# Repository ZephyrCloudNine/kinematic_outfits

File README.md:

# kinematic_dress_hw_fw
Project files for custom "kinematic" dress that uses servos to move parts of it in a wavy motion.
Firmware uses an ESP32-C3 Devkit module.
Servos used - SG90 along with PCA9685 servo driver to extend servo drive functionality.
Mechanical design done on Fusion 360.

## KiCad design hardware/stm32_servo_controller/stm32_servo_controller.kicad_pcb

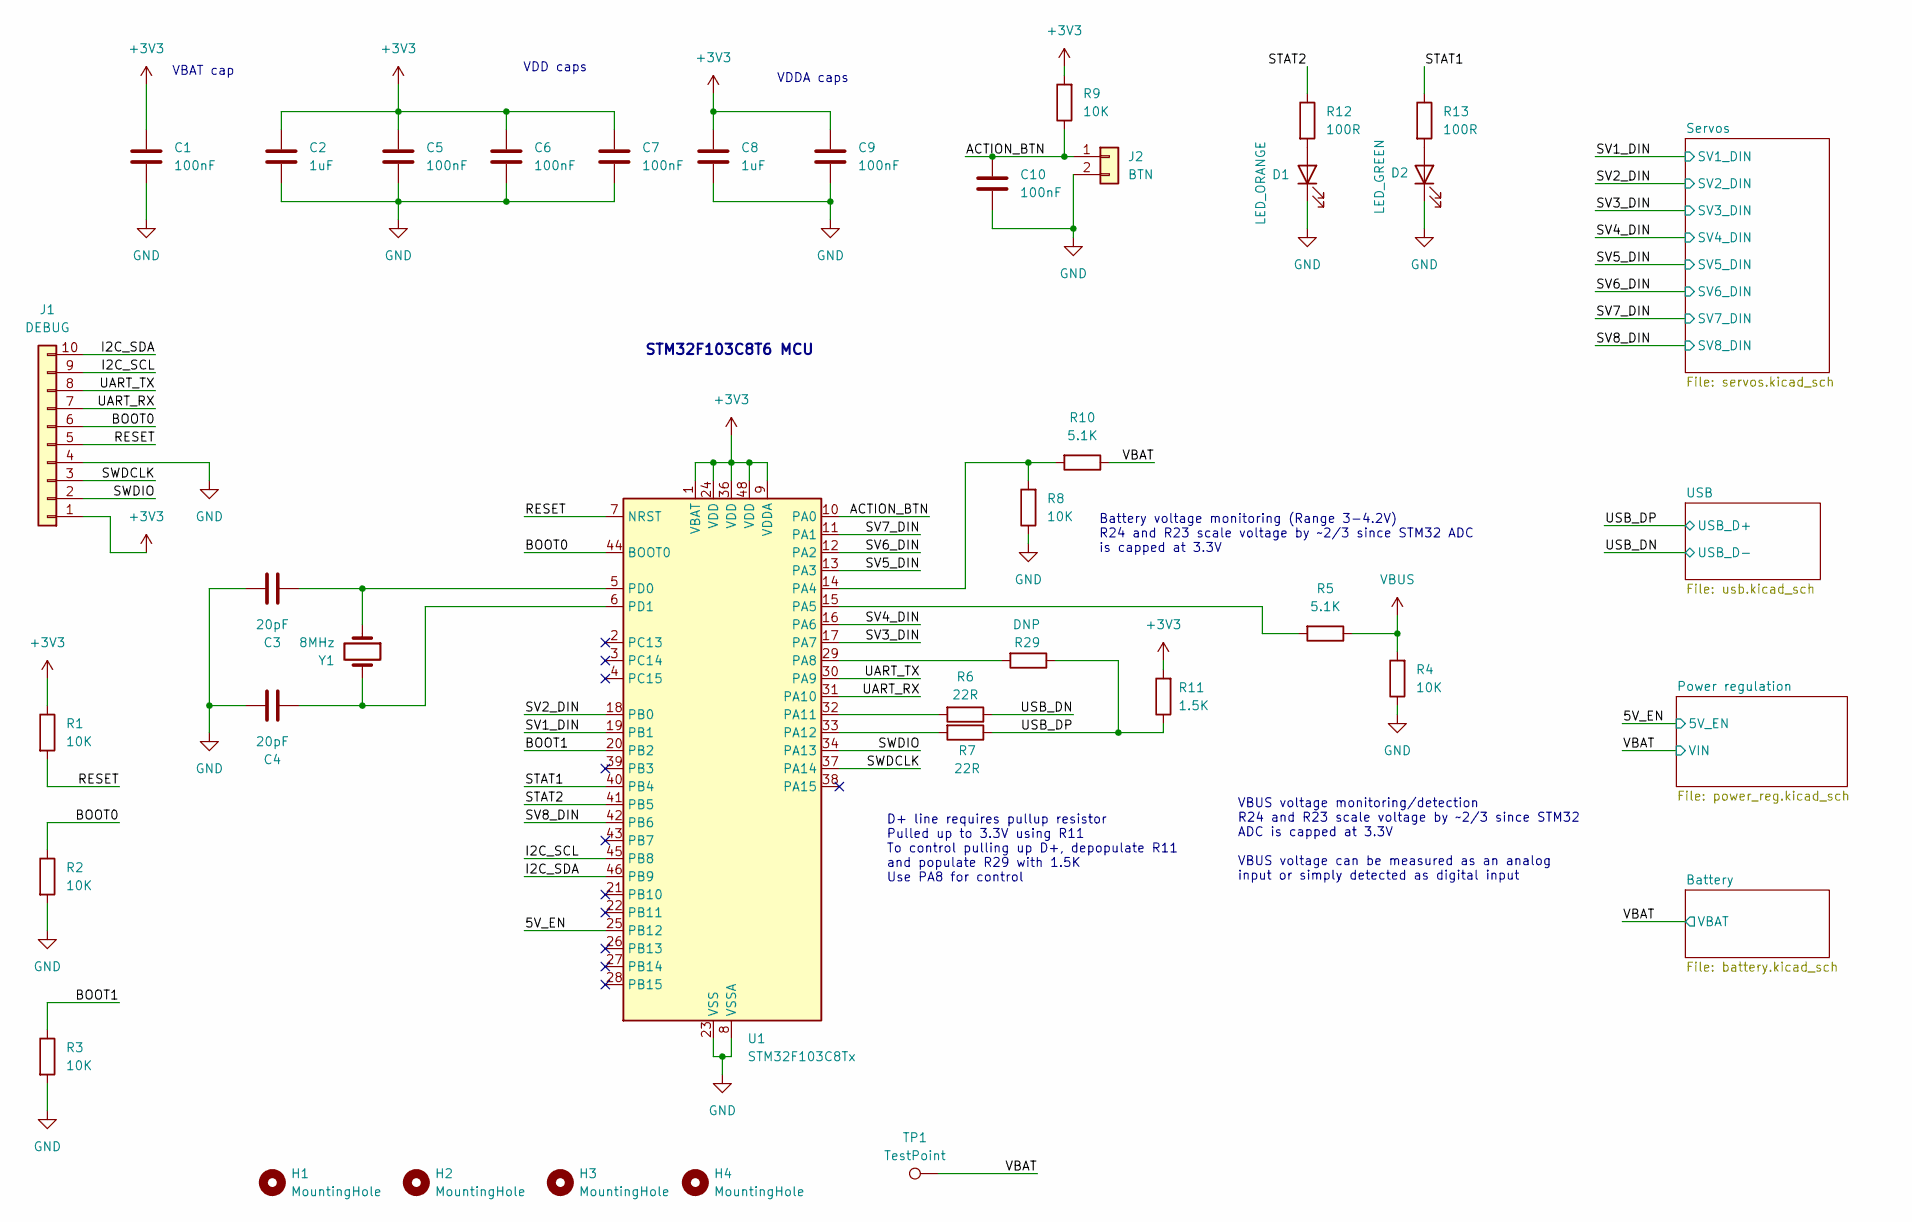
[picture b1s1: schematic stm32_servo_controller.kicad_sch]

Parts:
C1, C5, C6, C7, C9, C10: 100nF; C_0603_1608Metric
C2, C8: 1uF; C_0603_1608Metric
C3, C4: 20pF; C_0603_1608Metric
D1: LED_ORANGE; LED_0603_1608Metric
D2: LED_GREEN; LED_0603_1608Metric
H1, H2, H3, H4: MountingHole; MountingHole_3.2mm_M3
J1: DEBUG; PinHeader_1x10_P2.54mm_Vertical
J2: BTN; PinHeader_1x02_P2.54mm_Vertical
R1, R2, R3, R4, R8, R9: 10K; R_0603_1608Metric
R5, R10: 5.1K; R_0603_1608Metric
R6, R7: 22R; R_0603_1608Metric
R11: 1.5K; R_0603_1608Metric
R12, R13: 100R; R_0603_1608Metric
R29: DNP; R_0603_1608Metric
TP1: TestPoint; TestPoint_Pad_D1.0mm
U1: STM32F103C8Tx; LQFP-48_7x7mm_P0.5mm
Y1: 8MHz; Crystal_HC49-4H_Vertical

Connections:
+3V3: C1.1, C2.1, C5.1, C6.1, C7.1, C8.1, C9.1, J1.1, R1.1, R9.2, R11.2, U1.1 (VBAT), U1.9 (VDDA), U1.24 (VDD), U1.36 (VDD), U1.48 (VDD); also elsewhere on the board
/5V_EN: U1.25 (PB12); also elsewhere on the board
/ACTION_BTN: C10.1, J2.1, R9.1, U1.10 (PA0)
/BOOT0: J1.6, R2.1, U1.44 (BOOT0)
/BOOT1: R3.1, U1.20 (PB2)
/I2C_SCL: J1.9, U1.45 (PB8)
/I2C_SDA: J1.10, U1.46 (PB9)
/RESET: J1.5, R1.2, U1.7 (NRST)
/STAT1: R13.1, U1.40 (PB4)
/STAT2: R12.1, U1.41 (PB5)
/SV1_DIN: U1.19 (PB1); also elsewhere on the board
/SV2_DIN: U1.18 (PB0); also elsewhere on the board
/SV3_DIN: U1.17 (PA7); also elsewhere on the board
/SV4_DIN: U1.16 (PA6); also elsewhere on the board
/SV5_DIN: U1.13 (PA3); also elsewhere on the board
/SV6_DIN: U1.12 (PA2); also elsewhere on the board
/SV7_DIN: U1.11 (PA1); also elsewhere on the board
/SV8_DIN: U1.42 (PB6); also elsewhere on the board
/SWDCLK: J1.3, U1.37 (PA14)
/SWDIO: J1.2, U1.34 (PA13)
/UART_RX: J1.7, U1.31 (PA10)
/UART_TX: J1.8, U1.30 (PA9)
/USB_DN: R6.1; also elsewhere on the board
/USB_DP: R7.1, R11.1, R29.1; also elsewhere on the board
/VBAT: R10.1, TP1.1; also elsewhere on the board
GND: C1.2, C2.2, C3.2, C4.2, C5.2, C6.2, C7.2, C8.2, C9.2, C10.2, D1.1 (K), D2.1 (K), J1.4, J2.2, R2.2, R3.2, R4.1, R8.1, U1.8 (VSSA), U1.23 (VSS), U1.35 (VSS), U1.47 (VSS); also elsewhere on the board
unnamed: D1.2 (A), R12.2
unnamed: D2.2 (A), R13.2
unnamed: R8.2, R10.2, U1.14 (PA4)
unnamed: R5.2, U1.15 (PA5)
unnamed: R29.2, U1.29 (PA8)
unnamed: R6.2, U1.32 (PA11)
unnamed: R7.2, U1.33 (PA12)
unnamed: C3.1, U1.5 (PD0), Y1.1
unnamed: C4.1, U1.6 (PD1), Y1.2
VBUS: R4.2, R5.1; also elsewhere on the board

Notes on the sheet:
STM32F103C8T6 MCU
VDDA caps
VBAT cap
VDD caps
D+ line requires pullup resistor Pulled up to 3.3V using R11 To control pulling up D+, depopulate R11 and populate R29 with 1.5K Use PA8 for control
VBUS voltage monitoring/detection R24 and R23 scale voltage by ~2/3 since STM32 ADC is capped at 3.3V VBUS voltage can be measured as an analog input or simply detected as digital input
Battery voltage monitoring (Range 3-4.2V) R24 and R23 scale voltage by ~2/3 since STM32 ADC is capped at 3.3V

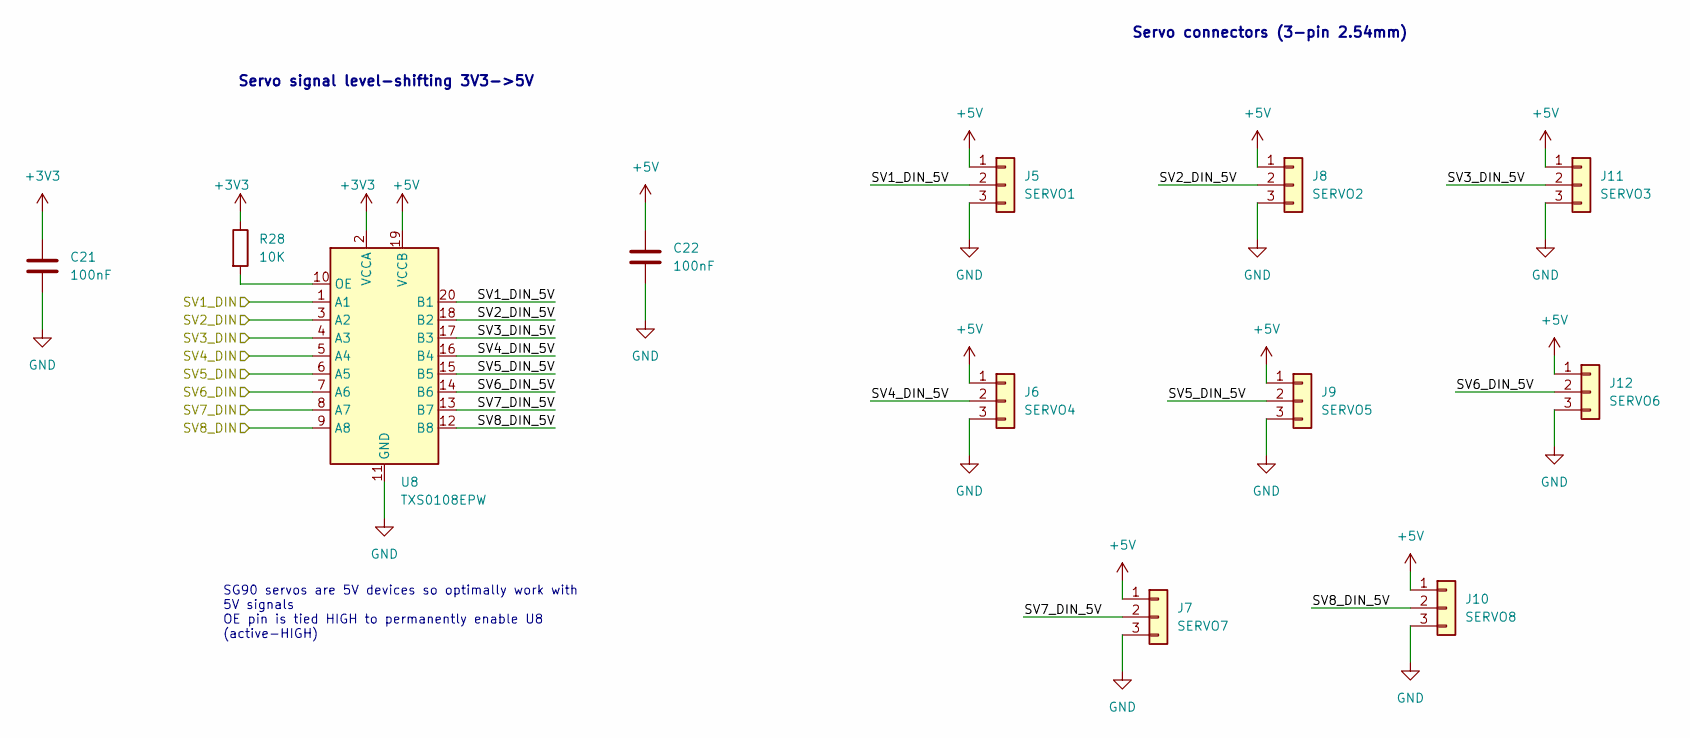
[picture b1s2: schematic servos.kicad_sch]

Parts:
C21, C22: 100nF; C_0603_1608Metric
J5: SERVO1; JST_XH_B3B-XH-A_1x03_P2.50mm_Vertical
J6: SERVO4; JST_XH_B3B-XH-A_1x03_P2.50mm_Vertical
J7: SERVO7; JST_XH_B3B-XH-A_1x03_P2.50mm_Vertical
J8: SERVO2; JST_XH_B3B-XH-A_1x03_P2.50mm_Vertical
J9: SERVO5; JST_XH_B3B-XH-A_1x03_P2.50mm_Vertical
J10: SERVO8; JST_XH_B3B-XH-A_1x03_P2.50mm_Vertical
J11: SERVO3; JST_XH_B3B-XH-A_1x03_P2.50mm_Vertical
J12: SERVO6; JST_XH_B3B-XH-A_1x03_P2.50mm_Vertical
R28: 10K; R_0603_1608Metric
U8: TXS0108EPW; TSSOP-20_4.4x6.5mm_P0.65mm

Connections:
+3V3: C21.1, R28.1, U8.2 (VCCA); also elsewhere on the board
+5V: C22.1, J5.1, J6.1, J7.1, J8.1, J9.1, J10.1, J11.1, J12.1, U8.19 (VCCB); also elsewhere on the board
/SV1_DIN: U8.1 (A1); also elsewhere on the board
/SV2_DIN: U8.3 (A2); also elsewhere on the board
/SV3_DIN: U8.4 (A3); also elsewhere on the board
/SV4_DIN: U8.5 (A4); also elsewhere on the board
/SV5_DIN: U8.6 (A5); also elsewhere on the board
/SV6_DIN: U8.7 (A6); also elsewhere on the board
/SV7_DIN: U8.8 (A7); also elsewhere on the board
/SV8_DIN: U8.9 (A8); also elsewhere on the board
/Servos/SV1_DIN_5V: J5.2, U8.20 (B1)
/Servos/SV2_DIN_5V: J8.2, U8.18 (B2)
/Servos/SV3_DIN_5V: J11.2, U8.17 (B3)
/Servos/SV4_DIN_5V: J6.2, U8.16 (B4)
/Servos/SV5_DIN_5V: J9.2, U8.15 (B5)
/Servos/SV6_DIN_5V: J12.2, U8.14 (B6)
/Servos/SV7_DIN_5V: J7.2, U8.13 (B7)
/Servos/SV8_DIN_5V: J10.2, U8.12 (B8)
GND: C21.2, C22.2, J5.3, J6.3, J7.3, J8.3, J9.3, J10.3, J11.3, J12.3, U8.11 (GND); also elsewhere on the board
unnamed: R28.2, U8.10 (OE)

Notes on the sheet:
Servo signal level-shifting 3V3->5V
SG90 servos are 5V devices so optimally work with 5V signals OE pin is tied HIGH to permanently enable U8 (active-HIGH)
Servo connectors (3-pin 2.54mm)

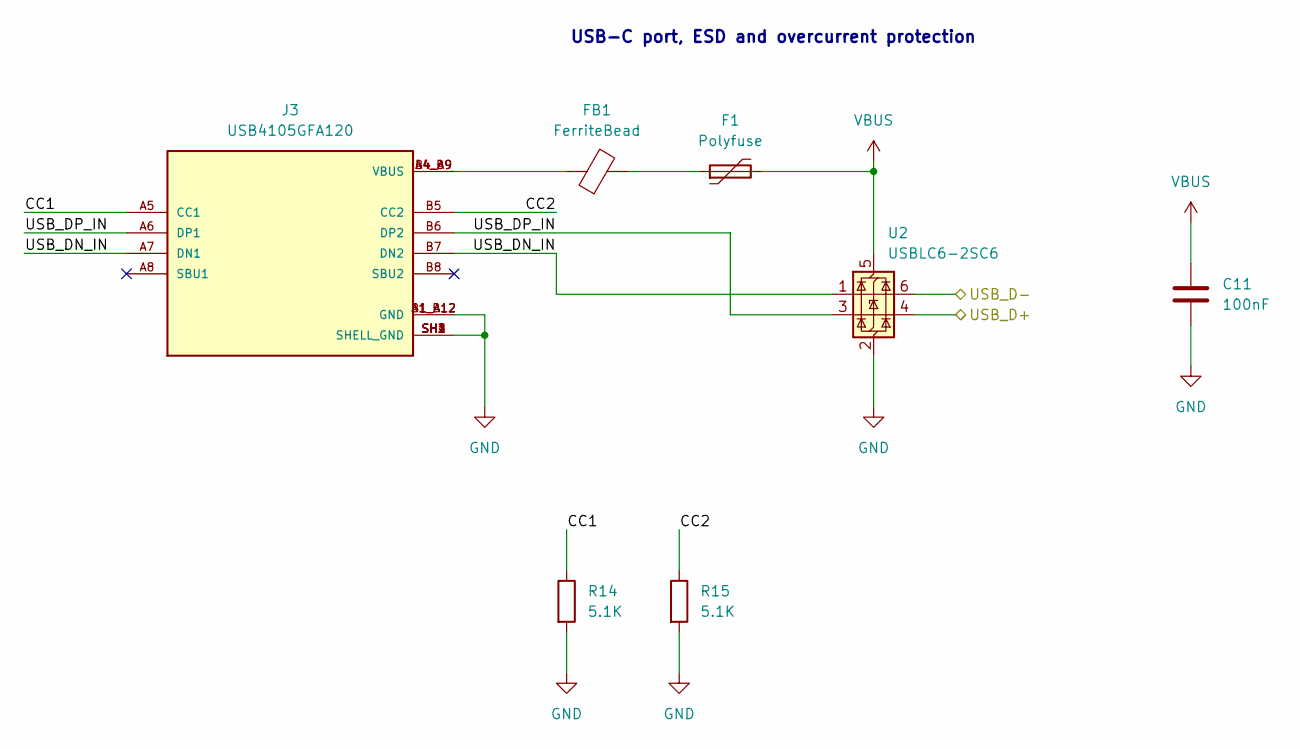
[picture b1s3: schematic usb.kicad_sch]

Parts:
C11: 100nF; C_0603_1608Metric
F1: Polyfuse; Fuse_1206_3216Metric
FB1: FerriteBead; L_0805_2012Metric
J3: USB4105GFA120; GCT_USB4105GFA120; PARTREV B3
R14, R15: 5.1K; R_0603_1608Metric
U2: USBLC6-2SC6; SOT-23-6

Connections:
/USB/CC1: J3.A5 (CC1), R14.1
/USB/CC2: J3.B5 (CC2), R15.1
/USB/USB_DN_IN: J3.A7 (DN1), J3.B7 (DN2), U2.1 (I/O1)
/USB/USB_DP_IN: J3.A6 (DP1), J3.B6 (DP2), U2.3 (I/O2)
/USB_DN: U2.6 (I/O1); also elsewhere on the board
/USB_DP: U2.4 (I/O2); also elsewhere on the board
GND: C11.2, J3.A1_B12 (GND), J3.B1_A12 (GND), J3.SH1 (SHELL_GND), J3.SH2 (SHELL_GND), J3.SH3 (SHELL_GND), J3.SH4 (SHELL_GND), R14.2, R15.2, U2.2 (GND); also elsewhere on the board
unnamed: F1.1, FB1.2
unnamed: FB1.1, J3.A4_B9 (VBUS), J3.B4_A9 (VBUS)
VBUS: C11.1, F1.2, U2.5 (VBUS); also elsewhere on the board

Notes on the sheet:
USB-C port, ESD and overcurrent protection

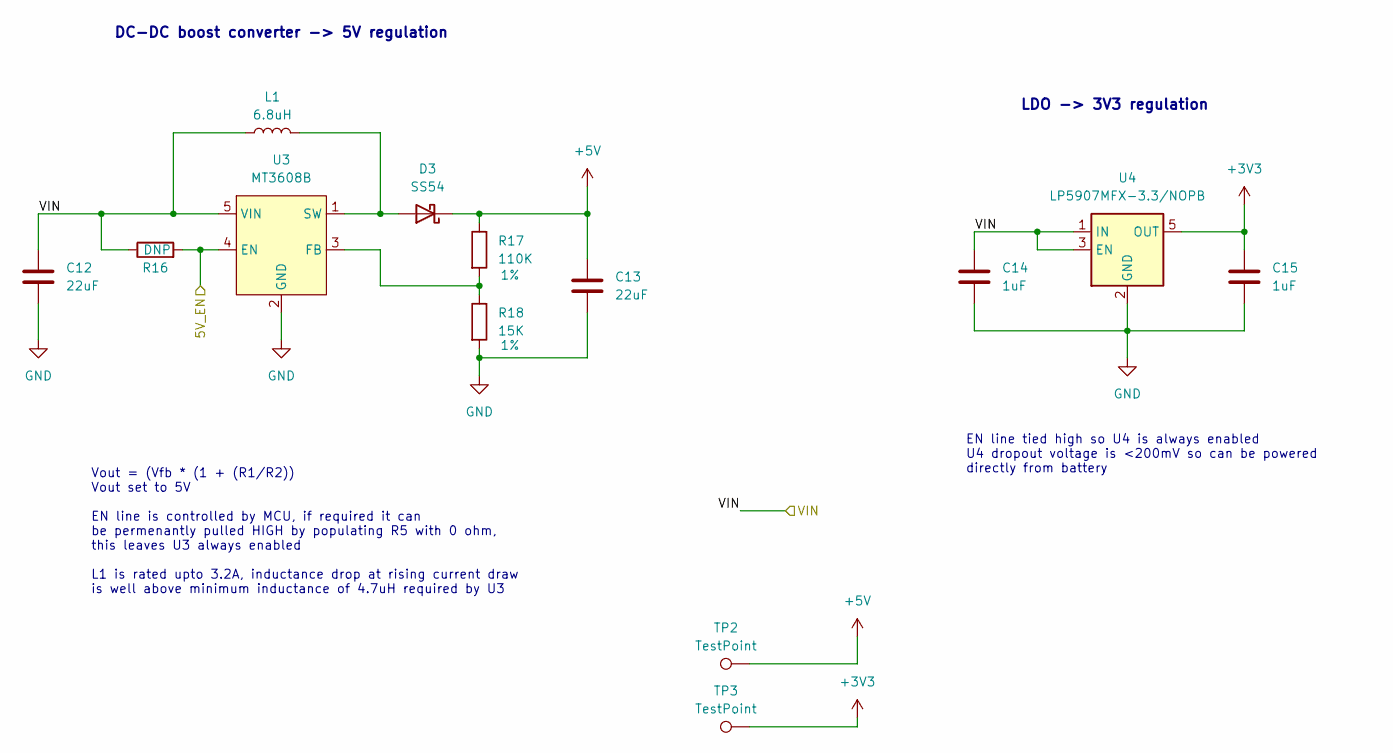
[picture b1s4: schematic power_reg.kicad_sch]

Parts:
C12, C13: 22uF; C_1206_3216Metric
C14, C15: 1uF; C_0603_1608Metric
D3: SS54; D_SMB
L1: 6.8uH; L_Sunlord_MWSA0503S
R16: DNP; R_0603_1608Metric
R17: 110K; R_0603_1608Metric; Tolerance 1%
R18: 15K; R_0603_1608Metric; Tolerance 1%
TP2, TP3: TestPoint; TestPoint_Pad_D1.0mm
U3: MT3608B; SOT-23-6
U4: LP5907MFX-3.3/NOPB; SOT-23-5

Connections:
+3V3: C15.1, TP3.1, U4.5 (OUT); also elsewhere on the board
+5V: C13.1, D3.1 (K), R17.1, TP2.1; also elsewhere on the board
/5V_EN: R16.2, U3.4 (EN); also elsewhere on the board
/VBAT: C12.1, C14.1, L1.1, R16.1, U3.5 (VIN), U4.1 (IN), U4.3 (EN); also elsewhere on the board
GND: C12.2, C13.2, C14.2, C15.2, R18.2, U3.2 (GND), U4.2 (GND); also elsewhere on the board
unnamed: D3.2 (A), L1.2, U3.1 (SW)
unnamed: R17.2, R18.1, U3.3 (FB)

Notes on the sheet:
DC-DC boost converter -> 5V regulation
Vout = (Vfb * (1 + (R1/R2)) Vout set to 5V EN line is controlled by MCU, if required it can be permenantly pulled HIGH by populating R5 with 0 ohm, this leaves U3 always enabled L1 is rated upto 3.2A, inductance drop at rising current draw is well above minimum inductance of 4.7uH required by U3
LDO -> 3V3 regulation
EN line tied high so U4 is always enabled U4 dropout voltage is <200mV so can be powered directly from battery

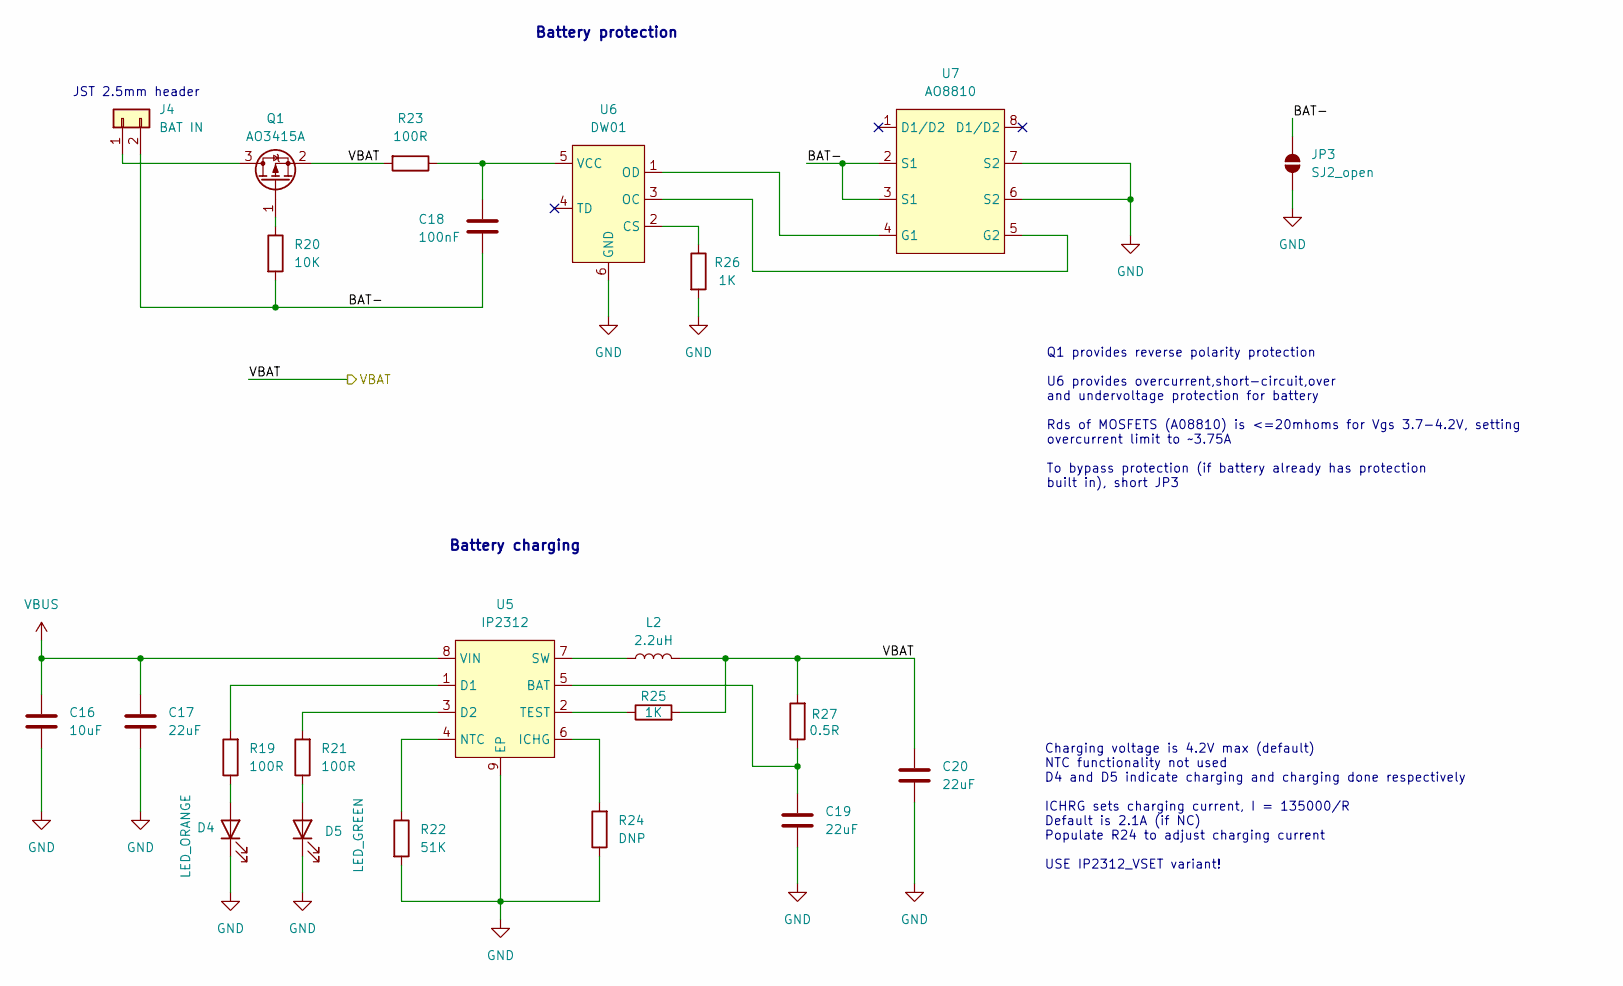
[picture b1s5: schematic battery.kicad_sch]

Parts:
C16: 10uF; C_0805_2012Metric
C17, C19, C20: 22uF; C_0805_2012Metric
C18: 100nF; C_0603_1608Metric
D4: LED_ORANGE; LED_0603_1608Metric
D5: LED_GREEN; LED_0603_1608Metric
J4: BAT IN; PinHeader_1x02_P2.54mm_Vertical
JP3: SJ2_open; SolderJumper-2_P1.3mm_Open_RoundedPad1.0x1.5mm
L2: 2.2uH; L_Sunlord_MWSA0503S
Q1: AO3415A; SOT-23
R19, R21, R23: 100R; R_0603_1608Metric
R20: 10K; R_0603_1608Metric
R22: 51K; R_0603_1608Metric
R24: DNP; R_0805_2012Metric
R25, R26: 1K; R_0603_1608Metric
R27: 0.5R; R_0805_2012Metric
U5: IP2312; HSOP-8-1EP_3.9x4.9mm_P1.27mm_EP2.3x2.3mm
U6: DW01; SOT-23-6
U7: AO8810; TSSOP-8_4.4x3mm_P0.65mm

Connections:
/Battery/BAT-: C18.2, J4.2, JP3.2 (B), R20.2, U7.2 (S1), U7.3 (S1)
/VBAT: C20.1, L2.2, Q1.2 (S), R23.2, R25.2, R27.2; also elsewhere on the board
GND: C16.2, C17.2, C19.2, C20.2, D4.1 (K), D5.1 (K), JP3.1 (A), R22.2, R24.1, R26.2, U5.9 (EP), U6.6 (GND), U7.6 (S2), U7.7 (S2); also elsewhere on the board
unnamed: D4.2 (A), R19.1
unnamed: D5.2 (A), R21.1
unnamed: J4.1, Q1.3 (D)
unnamed: Q1.1 (G), R20.1
unnamed: C19.1, R27.1, U5.5 (BAT)
unnamed: R19.2, U5.1 (D1)
unnamed: R21.2, U5.3 (D2)
unnamed: R24.2, U5.6 (ICHG)
unnamed: R22.1, U5.4 (NTC)
unnamed: L2.1, U5.7 (SW)
unnamed: R25.1, U5.2 (TEST)
unnamed: R26.1, U6.2 (CS)
unnamed: U6.3 (OC), U7.5 (G2)
unnamed: U6.1 (OD), U7.4 (G1)
unnamed: C18.1, R23.1, U6.5 (VCC)
VBUS: C16.1, C17.1, U5.8 (VIN); also elsewhere on the board

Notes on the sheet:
Charging voltage is 4.2V max (default) NTC functionality not used D4 and D5 indicate charging and charging done respectively ICHRG sets charging current, I = 135000/R Default is 2.1A (if NC) Populate R24 to adjust charging current USE IP2312_VSET variant!
Battery charging
JST 2.5mm header
Battery protection
Q1 provides reverse polarity protection U6 provides overcurrent,short-circuit,over and undervoltage protection for battery Rds of MOSFETS (A08810) is <=20mhoms for Vgs 3.7-4.2V, setting overcurrent limit to ~3.75A To bypass protection (if battery already has protection built in), short JP3

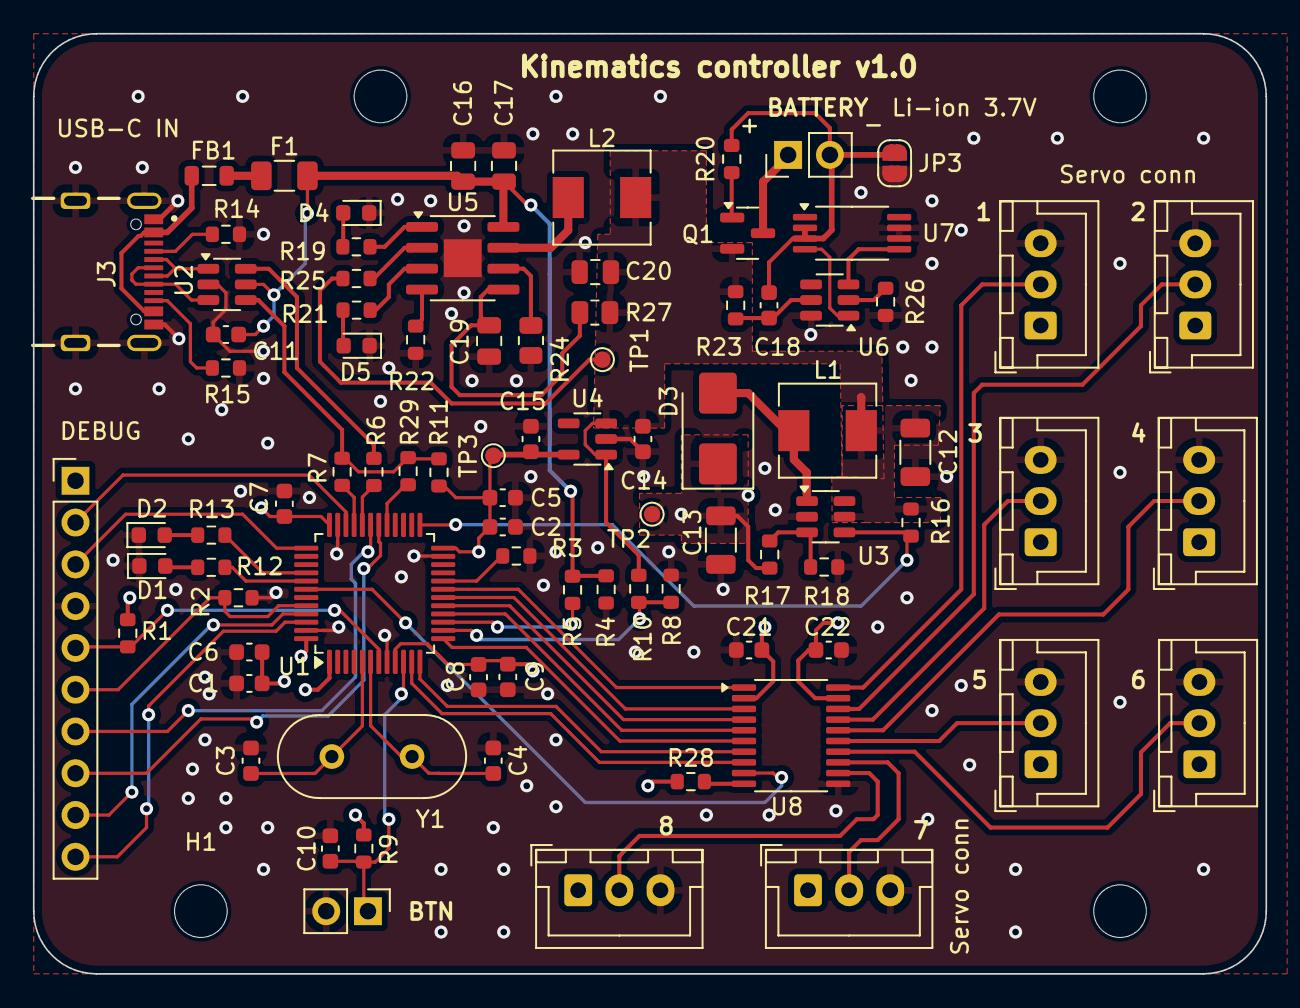
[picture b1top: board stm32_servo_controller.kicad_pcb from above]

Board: 4 copper layers, 74.9 x 57.1 mm, 90 parts (0 on the bottom side), 70 nets.

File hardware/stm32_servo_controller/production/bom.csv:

Designator,Footprint,Quantity,Value,LCSC Part #
"C1, C10, C11, C18, C21, C22, C5, C6, C7, C9",0603,10,100nF,
"C12, C13",1206,2,22uF,
"C14, C15, C2, C8",0603,4,1uF,
C16,0805,1,10uF,
"C17, C19, C20",0805,3,22uF	,
"C3, C4",0603,2,20pF,
"D1, D4",0603,2,LED_ORANGE,
"D2, D5",0603,2,LED_GREEN,
D3,D_SMB,1,SS54,
F1,1206,1,Polyfuse,
FB1,0805,1,FerriteBead,
J1,PinHeader_1x10_P2.54mm_Vertical,1,DEBUG,
J10,JST_XH_B3B-XH-A_1x03_P2.50mm_Vertical,1,SERVO8,
J11,JST_XH_B3B-XH-A_1x03_P2.50mm_Vertical,1,SERVO3,
J12,JST_XH_B3B-XH-A_1x03_P2.50mm_Vertical,1,SERVO6,
J2,PinHeader_1x02_P2.54mm_Vertical,1,BTN,
J3,GCT_USB4105GFA120,1,USB4105GFA120,
J4,PinHeader_1x02_P2.54mm_Vertical,1,BAT IN,
J5,JST_XH_B3B-XH-A_1x03_P2.50mm_Vertical,1,SERVO1,
J6,JST_XH_B3B-XH-A_1x03_P2.50mm_Vertical,1,SERVO4,
J7,JST_XH_B3B-XH-A_1x03_P2.50mm_Vertical,1,SERVO7,
J8,JST_XH_B3B-XH-A_1x03_P2.50mm_Vertical,1,SERVO2,
J9,JST_XH_B3B-XH-A_1x03_P2.50mm_Vertical,1,SERVO5,
L1,L_Sunlord_MWSA0503S,1,6.8uH,
L2,L_Sunlord_MWSA0503S,1,2.2uH,
Q1,SOT-23,1,AO3415A,
"R1, R2, R20, R28, R3, R4, R8, R9",0603,8,10K,
"R10, R14, R15, R5",0603,4,5.1K,
R11,0603,1,1.5K,
"R12, R13, R19, R21, R23",0603,5,100R,
R17,0603,1,110K,
R18,0603,1,15K,
R22,0603,1,51K,
"R25, R26",0603,2,1K,
R27,0805,1,0.5R,
"R6, R7",0603,2,22R,
"TP1, TP2, TP3",TestPoint_Pad_D1.0mm,3,TestPoint,
U1,LQFP-48_7x7mm_P0.5mm,1,STM32F103C8Tx,
U2,SOT-23-6,1,USBLC6-2SC6,
U3,SOT-23-6,1,MT3608B,
U4,SOT-23-5,1,LP5907MFX-3.3/NOPB,
U5,HSOP-8-1EP_3.9x4.9mm_P1.27mm_EP2.3x2.3mm,1,IP2312,
U6,SOT-23-6,1,DW01,
U7,TSSOP-8_4.4x3mm_P0.65mm,1,AO8810,
U8,TSSOP-20_4.4x6.5mm_P0.65mm,1,TXS0108EPW,
Y1,Crystal_HC49-4H_Vertical,1,8MHz,

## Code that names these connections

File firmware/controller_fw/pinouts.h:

#ifndef PINOUTS_H
#define PINOUTS_H

//ADC pins
#define VBUS_MON PA5
#define VBAT_MON PA4

//button GPIO
#define ACTION_BTN PA0

//Status LED GPIO's
#define STAT1_LED PB4
#define STAT2_LED PB5

//Boost conv 5V enable
#define _5V_EN PB12

//I2C interfacce
#define I2C_SDA B9
#define I2C_SCL PB8

//servo outputs
#define SV1_DOUT PB1
#define SV2_DOUT PB0
#define SV3_DOUT PA7
#define SV4_DOUT PA6
#define SV5_DOUT PA3
#define SV6_DOUT PA2
#define SV7_DOUT PA1
#define SV8_DOUT PB6

#endif

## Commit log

2024-05-21 init code to test servo on PCA9685
2024-05-21 test code to run 4x servos on any of the 2 PCA9685 drivers
2024-05-21 added FastLED code to control on-board RGB LED on ESP32C3-Devkit
2024-05-22 added function to manually tune each servo and parses Serial input -required to correctly assemble each servo unit -command is in string format: driver_id, channel_id, pulse_length
2024-05-27 WIP test FW 240524 -successful test demo of 7 servos fitted onto dress
2024-06-11 FW ver 20240611 -15 motors running asynchronously
2024-10-12 updated file structure -added seperate folders for firmware and hardware -added KICAD project folder for servo_controller PCB design -added gitignore
2024-10-18 STM32 servo controller PCB KICAD project files
    -STM32F103CT8G MCU
    -Battery protection and charging circuitry on-board (1S1P/2P) Li-ion
    -5V DC-DC converter and 3.3V regulation
    -8x outputs for controlling upto 8 servo motors (SG90, etc ) using 2.5mm 3 pin headers/connectors
    -SWD, UART and I2C ports broken out on 2.54mm headers
    -USB-C input for charging and USB device functionality on STM32
2024-10-20 updated PCB BOM file
2024-11-01 Sample test FW setup for PCB rev1
    -added seperate .h for pinout definitions
    -updated all definitions for pins
    -tested LED blinking and USB CDC
2024-11-01 added ADC functionality
    -tested VBAT and VBUS monitoring
    -added function to derive voltage reading from raw analog reading and resistor divider ratio
2024-11-01 tested servos output block
    -level shifting works as intended
    -PWM write used to test 5V servo outputs switching
2024-11-01 Test FW to check all functionality of rev1 PCB's
2024-11-01 updated test FW
    -added utility.bat to simplify and uploading FW over Arduino CLI
    -added controlling servos (only 2 used for testing)
    -Loop monitors battery voltage and halts servos if low battery
2024-11-11 updated test FW
2024-11-23 FW: added LED flash pattern to indicate controller startup
2024-11-23 added servo configs
2024-11-23 changes to startup sequence
2024-11-23 added averaging to readCorrectedVoltage() func
2024-11-23 added MillisTimer and PRDCServo_HT to src folder
2024-11-24 modified ServoHT class
    -added setLimits() func to store arbitary lower and upper limits in degrees
    -added readDir() func to determine direction of servo movement
2024-11-24 servo updating now uses soft-timer hence non-blocking. updates at 50Hz
2024-11-24 voltage readings are now done periodically and non-blocking
2024-11-24 added VBUS detection to disable system when it is being charged
2024-11-25 added low battery detection
    -checks VBAT against threshold
    -halts loop if VBAT < threshold
    -flashes red LED periodically for visual indication of low battery
2024-11-26 added macros to configure different device variants while keeping codebase generic
2024-11-26 added time hysteresis to low battery detection to avoid false triggers due to sag/spikes
2024-11-27 general updates and fixes
